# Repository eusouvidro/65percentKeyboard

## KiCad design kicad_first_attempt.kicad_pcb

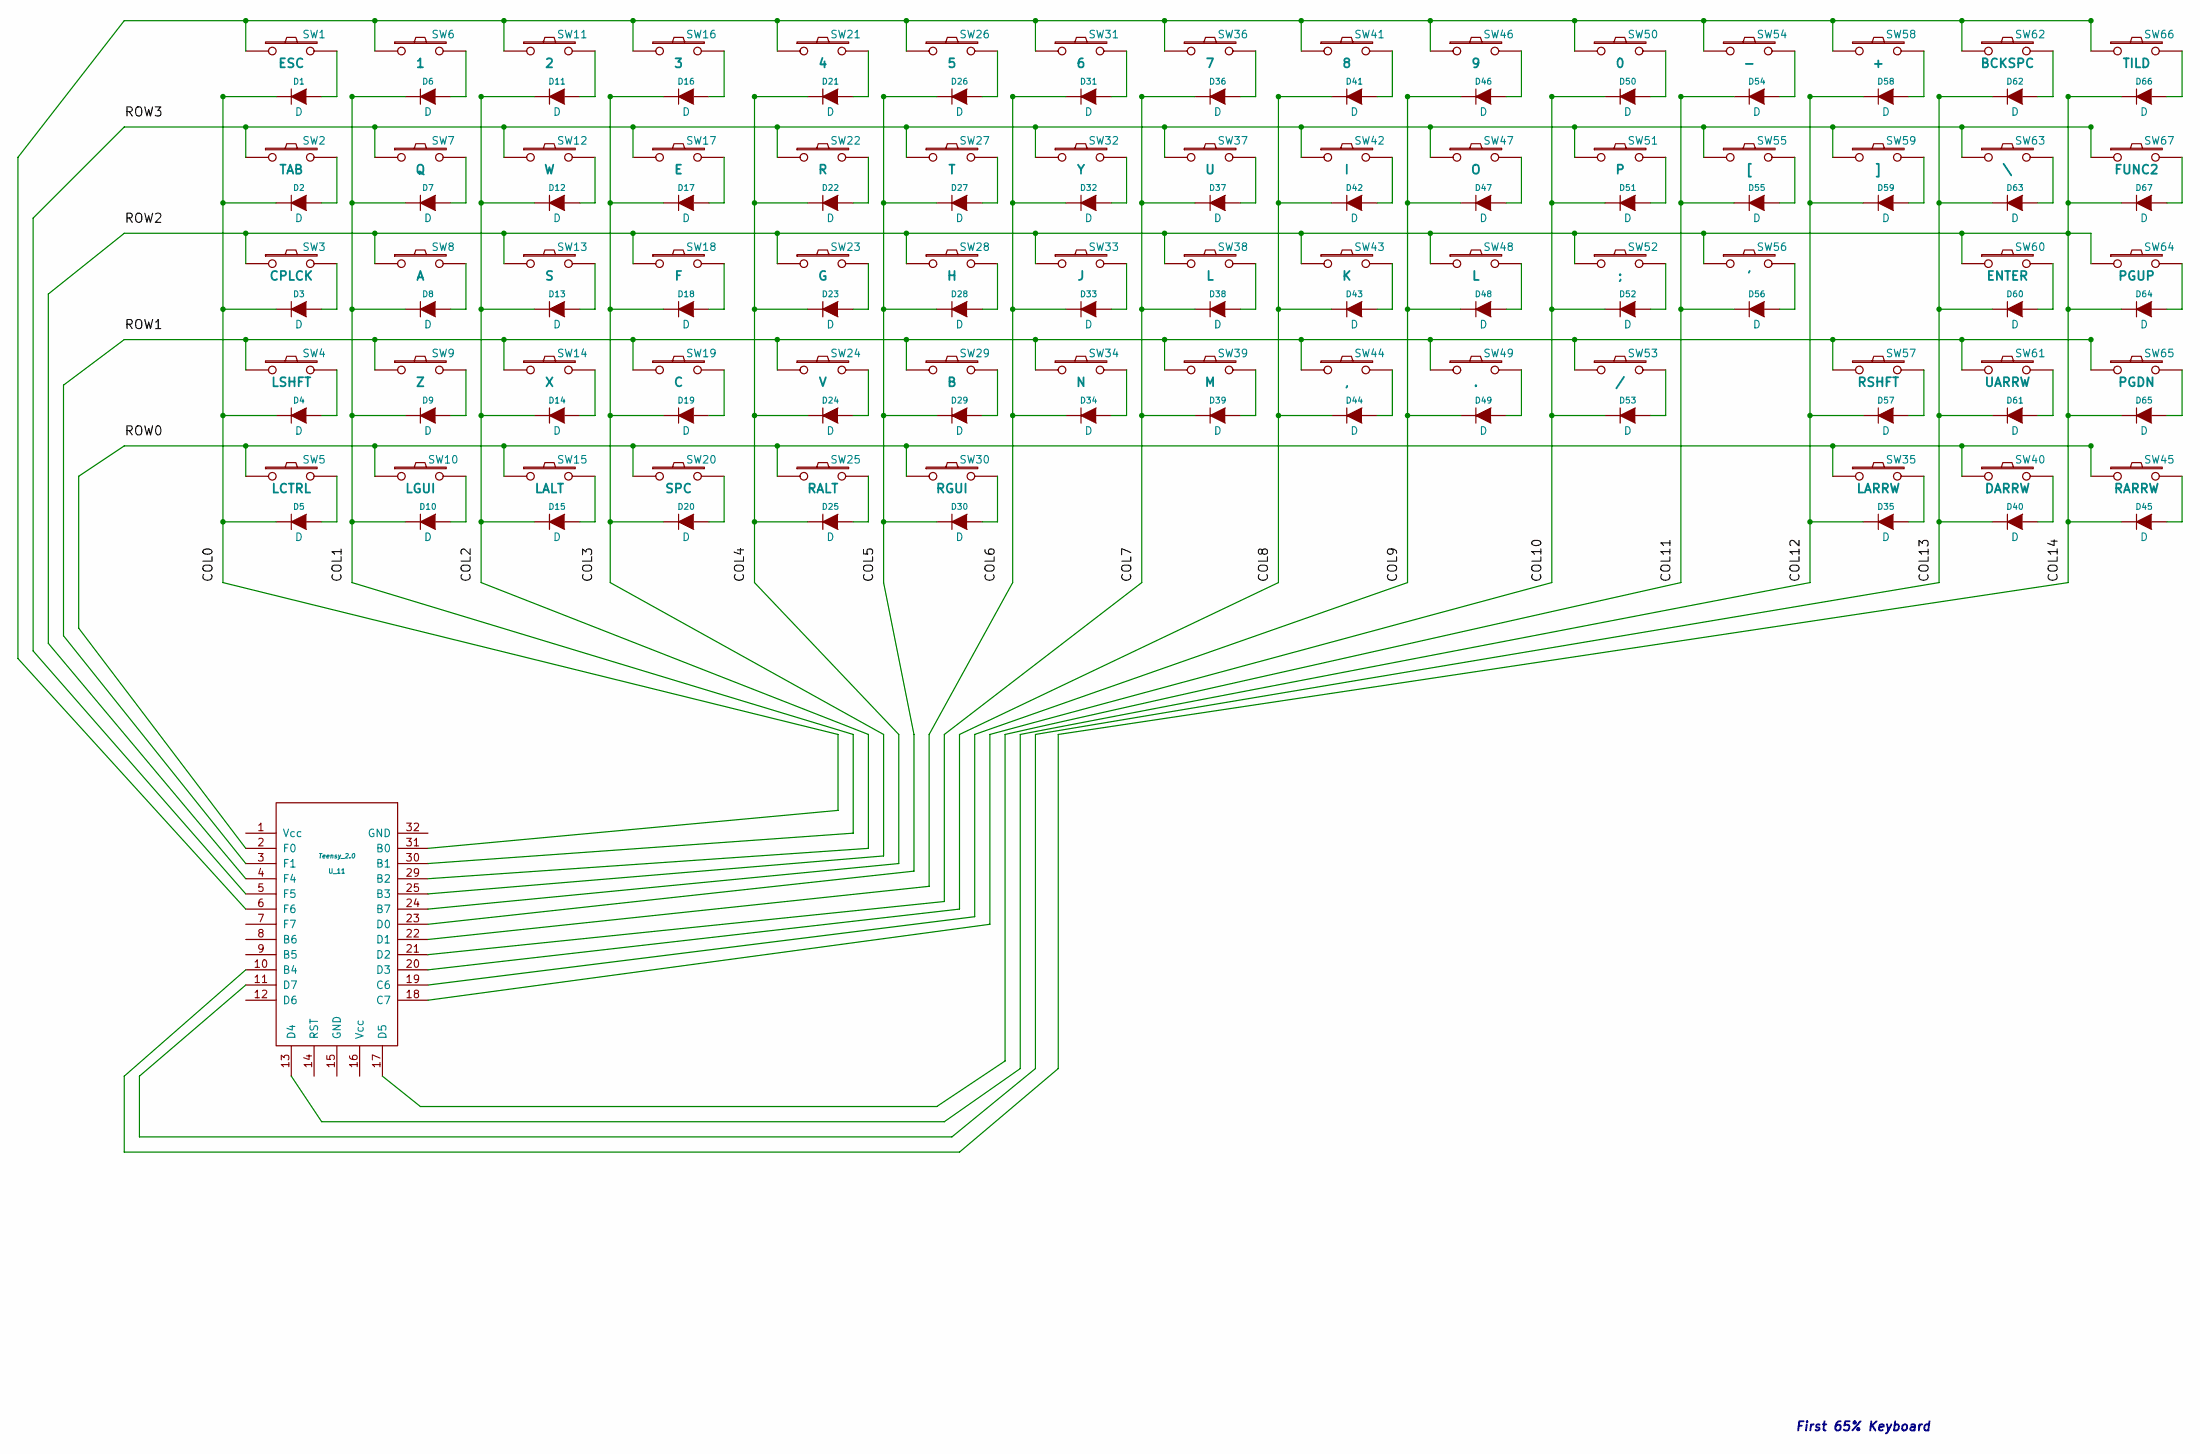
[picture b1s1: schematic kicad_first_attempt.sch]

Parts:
D1, D2, D3, D4, D5, D6, D7, D8, D9, D10, D11, D12, D13, D14, D15, D16, D17, D18, D19, D20, D21, D22, D23, D24, D25, D26, D27, D28, D29, D30, D31, D32, D33, D34, D35, D36, D37, D38, D39, D40, D41, D42, D43, D44, D45, D46, D47, D48, D49, D50, D51, D52, D53, D54, D55, D56, D57, D58, D59, D60, D61, D62, D63, D64, D65, D66, D67: D; CHERRY_MX_DIODE
SW1: ESC; CHERRY_PLATE_100H
SW2: TAB; CHERRY_PLATE_150H
SW3: CPLCK; CHERRY_PLATE_175H
SW4: LSHFT; CHERRY_PLATE_225H
SW5: LCTRL; CHERRY_PLATE_125H
SW6: 1; CHERRY_PLATE_100H
SW7: Q; CHERRY_PLATE_100H
SW8: A; CHERRY_PLATE_100H
SW9: Z; CHERRY_PLATE_100H
SW10: LGUI; CHERRY_PLATE_125H
SW11: 2; CHERRY_PLATE_100H
SW12: W; CHERRY_PLATE_100H
SW13: S; CHERRY_PLATE_100H
SW14: X; CHERRY_PLATE_100H
SW15: LALT; CHERRY_PLATE_125H
SW16: 3; CHERRY_PLATE_100H
SW17: E; CHERRY_PLATE_100H
SW18: F; CHERRY_PLATE_100H
SW19: C; CHERRY_PLATE_100H
SW20: SPC; CHERRY_PLATE_625H
SW21: 4; CHERRY_PLATE_100H
SW22: R; CHERRY_PLATE_100H
SW23: G; CHERRY_PLATE_100H
SW24: V; CHERRY_PLATE_100H
SW25: RALT; CHERRY_PLATE_125H
SW26: 5; CHERRY_PLATE_100H
SW27: T; CHERRY_PLATE_100H
SW28: H; CHERRY_PLATE_100H
SW29: B; CHERRY_PLATE_100H
SW30: RGUI; CHERRY_PLATE_125H
SW31: 6; CHERRY_PLATE_100H
SW32: Y; CHERRY_PLATE_100H
SW33: J; CHERRY_PLATE_100H
SW34: N; CHERRY_PLATE_100H
SW35: LARRW; CHERRY_PLATE_100H
SW36: 7; CHERRY_PLATE_100H
SW37: U; CHERRY_PLATE_100H
SW38, SW48: L; CHERRY_PLATE_100H
SW39: M; CHERRY_PLATE_100H
SW40: DARRW; CHERRY_PLATE_100H
SW41: 8; CHERRY_PLATE_100H
SW42: I; CHERRY_PLATE_100H
SW43: K; CHERRY_PLATE_100H
SW44: ,; CHERRY_PLATE_100H
SW45: RARRW; CHERRY_PLATE_100H
SW46: 9; CHERRY_PLATE_100H
SW47: O; CHERRY_PLATE_100H
SW49: .; CHERRY_PLATE_100H
SW50: 0; CHERRY_PLATE_100H
SW51: P; CHERRY_PLATE_100H
SW52: ;; CHERRY_PLATE_100H
SW53: /; CHERRY_PLATE_100H
SW54: -; CHERRY_PLATE_100H
SW55: [; CHERRY_PLATE_100H
SW56: '; CHERRY_PLATE_100H
SW57: RSHFT; CHERRY_PLATE_175H
SW58: +; CHERRY_PLATE_100H
SW59: ]; CHERRY_PLATE_100H
SW60: ENTER; CHERRY_PLATE_225H
SW61: UARRW; CHERRY_PLATE_100H
SW62: BCKSPC; CHERRY_PLATE_200H
SW63: \\; CHERRY_PLATE_150H
SW64: PGUP; CHERRY_PLATE_100H
SW65: PGDN; CHERRY_PLATE_100H
SW66: TILD; CHERRY_PLATE_100H
SW67: FUNC2; CHERRY_PLATE_100H
U_11: Teensy_2.0; TEENSY_2.0

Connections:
unnamed: D1.1 (K), D2.1 (K), D3.1 (K), D4.1 (K), D5.1 (K), U_11.31 (B0)
unnamed: D1.2 (A), SW1.2
unnamed: D2.2 (A), SW2.2
unnamed: D3.2 (A), SW3.2
unnamed: D4.2 (A), SW4.2
unnamed: D5.2 (A), SW5.2
unnamed: D6.2 (A), SW6.2
unnamed: D7.2 (A), SW7.2
unnamed: D8.2 (A), SW8.2
unnamed: D9.2 (A), SW9.2
unnamed: D6.1 (K), D7.1 (K), D8.1 (K), D9.1 (K), D10.1 (K), U_11.30 (B1)
unnamed: D10.2 (A), SW10.2
unnamed: D11.1 (K), D12.1 (K), D13.1 (K), D14.1 (K), D15.1 (K), U_11.29 (B2)
unnamed: D11.2 (A), SW11.2
unnamed: D12.2 (A), SW12.2
unnamed: D13.2 (A), SW13.2
unnamed: D14.2 (A), SW14.2
unnamed: D15.2 (A), SW15.2
unnamed: D16.1 (K), D17.1 (K), D18.1 (K), D19.1 (K), D20.1 (K), U_11.25 (B3)
unnamed: D16.2 (A), SW16.2
unnamed: D17.2 (A), SW17.2
unnamed: D18.2 (A), SW18.2
unnamed: D19.2 (A), SW19.2
unnamed: D20.2 (A), SW20.2
unnamed: D21.1 (K), D22.1 (K), D23.1 (K), D24.1 (K), D25.1 (K), U_11.24 (B7)
unnamed: D21.2 (A), SW21.2
unnamed: D22.2 (A), SW22.2
unnamed: D23.2 (A), SW23.2
unnamed: D24.2 (A), SW24.2
unnamed: D25.2 (A), SW25.2
unnamed: D26.1 (K), D27.1 (K), D28.1 (K), D29.1 (K), D30.1 (K), U_11.23 (D0)
unnamed: D26.2 (A), SW26.2
unnamed: D27.2 (A), SW27.2
unnamed: D28.2 (A), SW28.2
unnamed: D29.2 (A), SW29.2
unnamed: D30.2 (A), SW30.2
unnamed: D31.1 (K), D32.1 (K), D33.1 (K), D34.1 (K), U_11.22 (D1)
unnamed: D31.2 (A), SW31.2
unnamed: D32.2 (A), SW32.2
unnamed: D33.2 (A), SW33.2
unnamed: D34.2 (A), SW34.2
unnamed: D35.1 (K), D57.1 (K), D58.1 (K), D59.1 (K), U_11.13 (D4)
unnamed: D35.2 (A), SW35.2
unnamed: D36.1 (K), D37.1 (K), D38.1 (K), D39.1 (K), U_11.21 (D2)
unnamed: D36.2 (A), SW36.2
unnamed: D37.2 (A), SW37.2
unnamed: D38.2 (A), SW38.2
unnamed: D39.2 (A), SW39.2
unnamed: D40.1 (K), D60.1 (K), D61.1 (K), D62.1 (K), D63.1 (K), U_11.11 (D7)
unnamed: D40.2 (A), SW40.2
unnamed: D41.1 (K), D42.1 (K), D43.1 (K), D44.1 (K), U_11.20 (D3)
unnamed: D41.2 (A), SW41.2
unnamed: D42.2 (A), SW42.2
unnamed: D43.2 (A), SW43.2
unnamed: D44.2 (A), SW44.2
unnamed: D45.1 (K), D64.1 (K), D65.1 (K), D66.1 (K), D67.1 (K), SW3.1, SW8.1, SW13.1, SW18.1, SW23.1, SW28.1, SW33.1, SW38.1, SW43.1, SW48.1, SW52.1, SW56.1, SW60.1, SW64.1, U_11.4 (F4), U_11.10 (B4)
unnamed: D45.2 (A), SW45.2
unnamed: D46.1 (K), D47.1 (K), D48.1 (K), D49.1 (K), U_11.19 (C6)
unnamed: D46.2 (A), SW46.2
unnamed: D47.2 (A), SW47.2
unnamed: D48.2 (A), SW48.2
unnamed: D49.2 (A), SW49.2
unnamed: D50.1 (K), D51.1 (K), D52.1 (K), D53.1 (K), U_11.18 (C7)
unnamed: D50.2 (A), SW50.2
unnamed: D51.2 (A), SW51.2
unnamed: D52.2 (A), SW52.2
unnamed: D53.2 (A), SW53.2
unnamed: D54.1 (K), D55.1 (K), D56.1 (K), U_11.17 (D5)
unnamed: D54.2 (A), SW54.2
unnamed: D55.2 (A), SW55.2
unnamed: D56.2 (A), SW56.2
unnamed: D57.2 (A), SW57.2
unnamed: D58.2 (A), SW58.2
unnamed: D59.2 (A), SW59.2
unnamed: D60.2 (A), SW60.2
unnamed: D61.2 (A), SW61.2
unnamed: D62.2 (A), SW62.2
unnamed: D63.2 (A), SW63.2
unnamed: D64.2 (A), SW64.2
unnamed: D65.2 (A), SW65.2
unnamed: D66.2 (A), SW66.2
unnamed: D67.2 (A), SW67.2
unnamed: SW1.1, SW6.1, SW11.1, SW16.1, SW21.1, SW26.1, SW31.1, SW36.1, SW41.1, SW46.1, SW50.1, SW54.1, SW58.1, SW62.1, SW66.1, U_11.6 (F6)
unnamed: SW5.1, SW10.1, SW15.1, SW20.1, SW25.1, SW30.1, SW35.1, SW40.1, SW45.1, U_11.2 (F0)
unnamed: SW2.1, SW7.1, SW12.1, SW17.1, SW22.1, SW27.1, SW32.1, SW37.1, SW42.1, SW47.1, SW51.1, SW55.1, SW59.1, SW63.1, SW67.1, U_11.5 (F5)
unnamed: SW4.1, SW9.1, SW14.1, SW19.1, SW24.1, SW29.1, SW34.1, SW39.1, SW44.1, SW49.1, SW53.1, SW57.1, SW61.1, SW65.1, U_11.3 (F1)

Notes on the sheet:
First 65% Keyboard

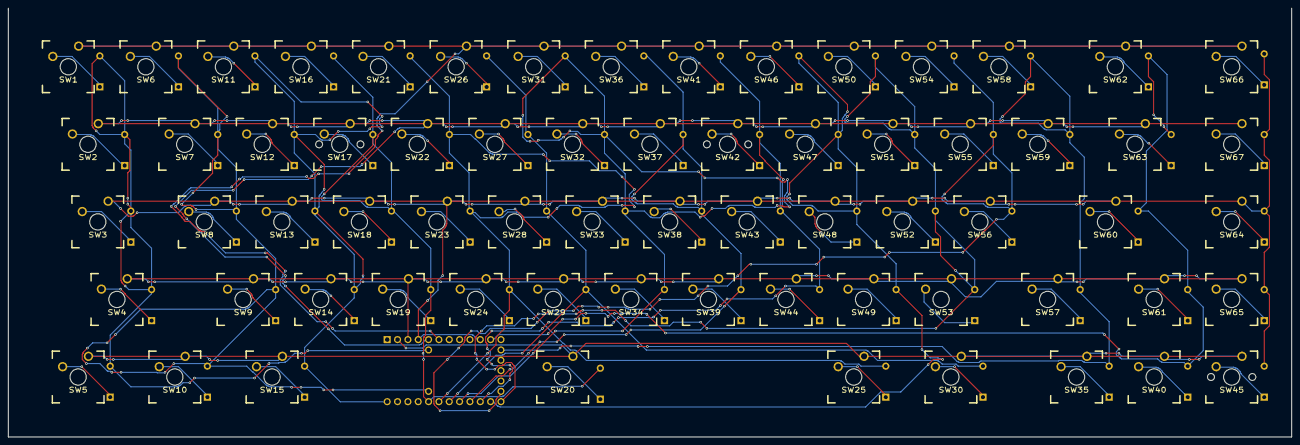
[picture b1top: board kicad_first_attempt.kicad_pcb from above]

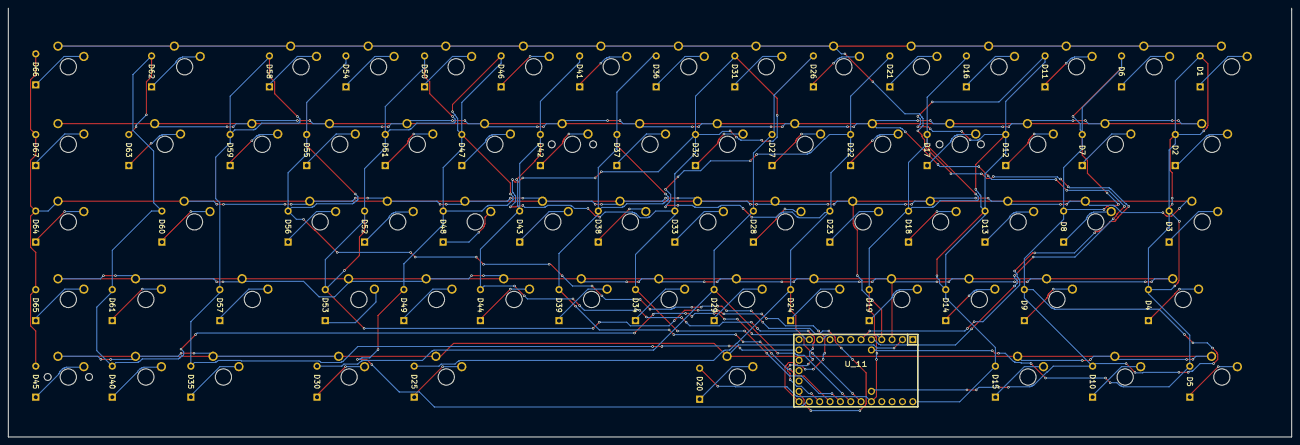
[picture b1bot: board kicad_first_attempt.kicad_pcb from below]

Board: 2 copper layers, 315.2 x 105.3 mm, 135 parts (68 on the bottom side), 86 nets.

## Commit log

2015-12-24 initial push
2015-12-24 removing README.md[A
